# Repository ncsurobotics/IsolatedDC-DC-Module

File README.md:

# IsolatedDC-DC-Module
SWIX Isolated DC/DC Project. KiCAD and Project Description

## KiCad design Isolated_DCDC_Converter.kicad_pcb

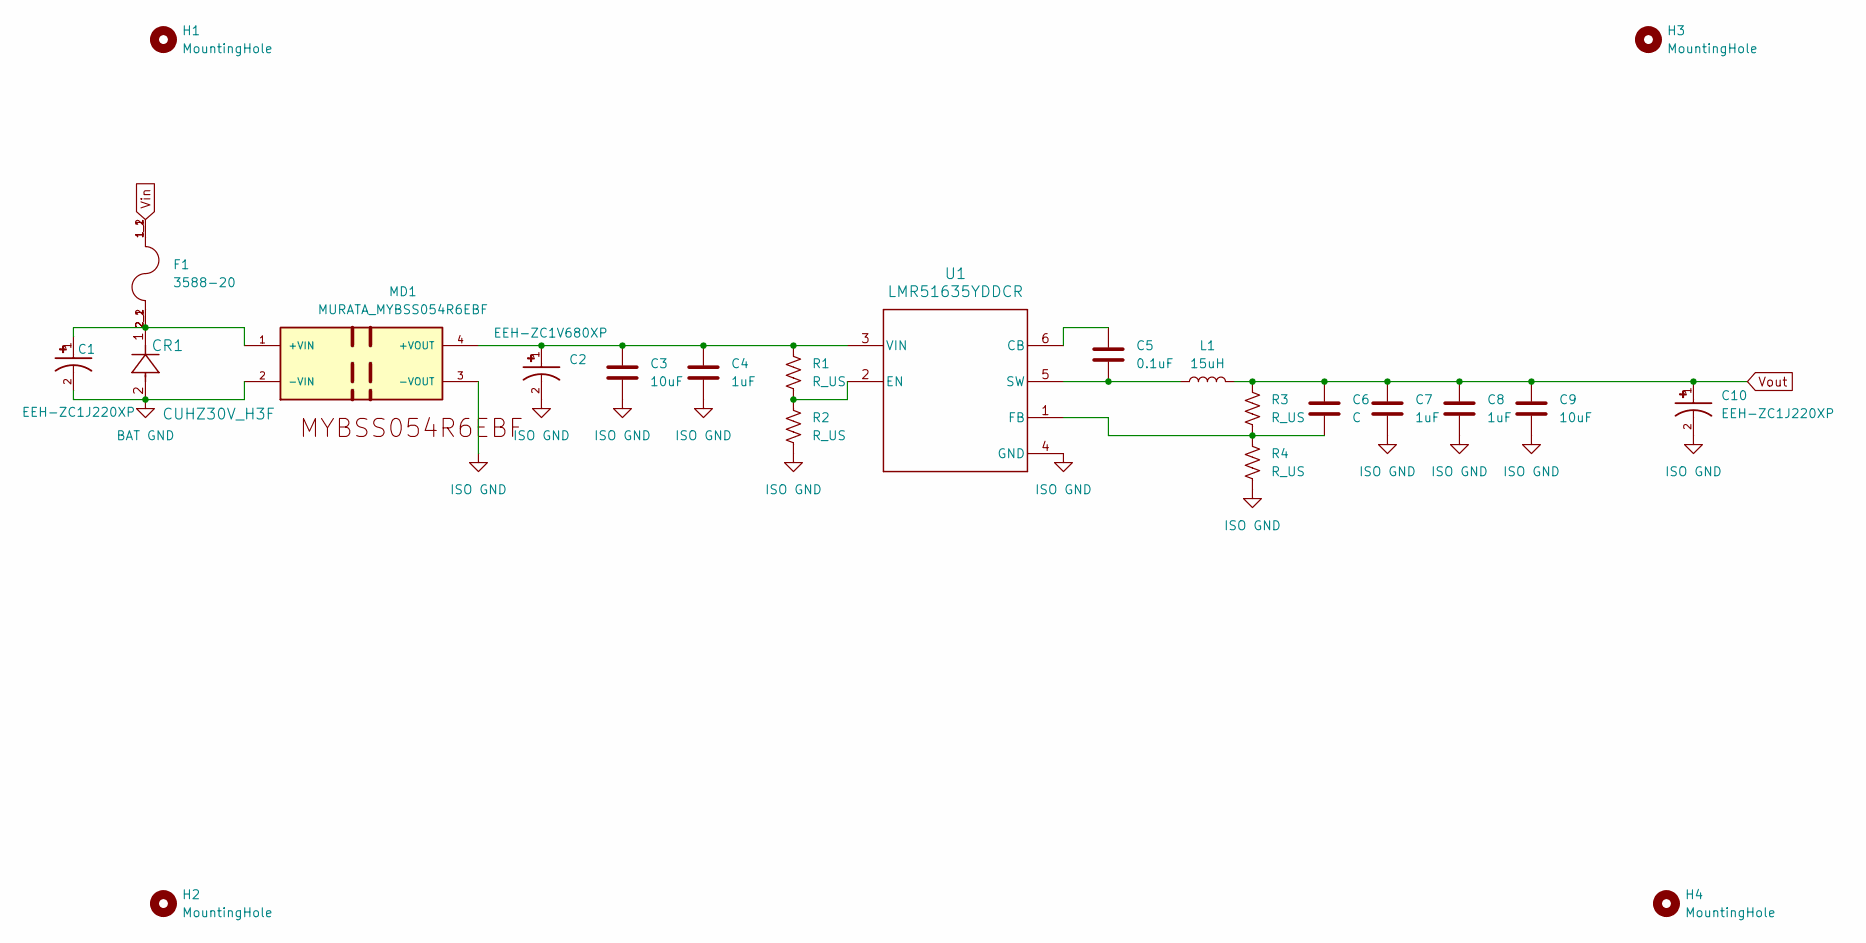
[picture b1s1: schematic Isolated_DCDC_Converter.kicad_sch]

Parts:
C1, C10: EEH-ZC1J220XP; CAP_EEH-ZC1J220XP; PARTREV 1-Sep-25
C2: EEH-ZC1V680XP; CAP_EEH-ZC1V680XP; PARTREV 1-Sep-25
C3, C9: 10uF; C_1206_3216Metric_Pad1.33x1.80mm_HandSolder
C4, C7, C8: 1uF; C_0603_1608Metric_Pad1.08x0.95mm_HandSolder
C5: 0.1uF; C_0603_1608Metric_Pad1.08x0.95mm_HandSolder
C6: C; C_0603_1608Metric_Pad1.08x0.95mm_HandSolder
CR1: CUHZ30V_H3F; SOD-323HEUS2H_TOS-L
F1: 3588-20; FUSE_3588-20; PARTREV E
H1, H2, H3, H4: MountingHole; MountingHole_2.5mm_Pad_TopBottom
L1: 15uH; SRP5030HMT2R2M
MD1: MURATA_MYBSS054R6EBF; MURATA_MYBSS054R6EBF_0
R1, R2, R3, R4: R_US; R_0603_1608Metric_Pad0.98x0.95mm_HandSolder
U1: LMR51635YDDCR; DDC0006A-MFG

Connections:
BAT GND: C1.2, CR1.2, MD1.2 (-VIN)
ISO GND: C2.2, C3.2, C4.2, C7.2, C8.2, C9.2, C10.2, MD1.3 (-VOUT), R2.2, R4.2, U1.4 (GND)
unnamed: C1.1, CR1.1, F1.2_1, F1.2_2, MD1.1 (+VIN)
unnamed: C2.1, C3.1, C4.1, MD1.4 (+VOUT), R1.1, U1.3 (VIN)
unnamed: C5.1, U1.6 (CB)
unnamed: R1.2, R2.1, U1.2 (EN)
unnamed: C6.2, R3.2, R4.1, U1.1 (FB)
unnamed: C5.2, L1.1, U1.5 (SW)
Vin: F1.1_1, F1.1_2
Vout: C6.1, C7.1, C8.1, C9.1, C10.1, L1.2, R3.1

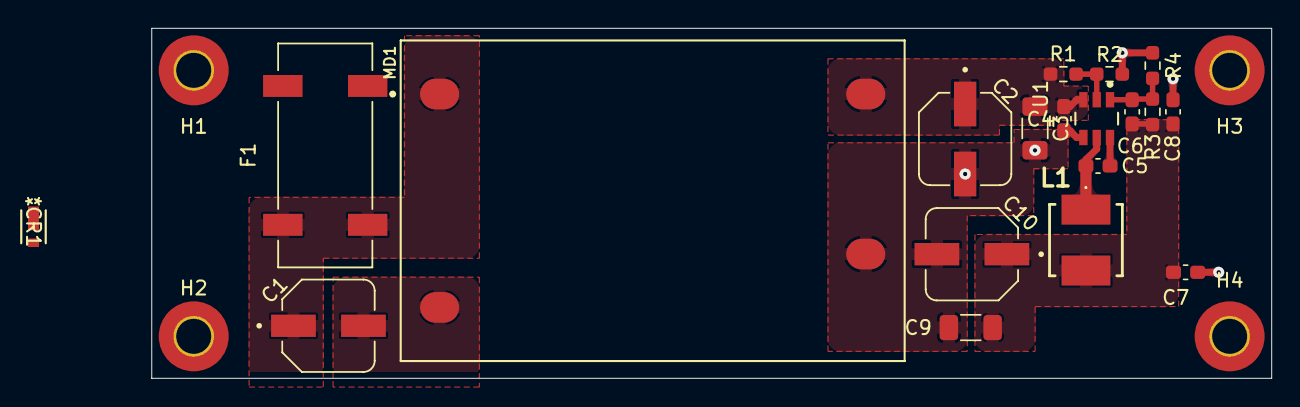
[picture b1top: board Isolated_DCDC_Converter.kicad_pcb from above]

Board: 2 copper layers, 80.0 x 25.0 mm, 23 parts (0 on the bottom side), 10 nets.
